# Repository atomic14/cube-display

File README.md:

# Cube Display

This is a work in progress project.

I'm currently testing the first set of PCBs. There will be updates as I find issues!

You can see some of the testing so far on my YouTube channel: [atomic14](https://www.youtube.com/@atomic14).

The demo above is using the code from [here](https://github.com/atomic14/ESP32-LSM6DS3-Demo).

# Files

- display-board: 14 segment display board
- main-board: main board for the display-board
- main-board-tft: WIP - not complete.

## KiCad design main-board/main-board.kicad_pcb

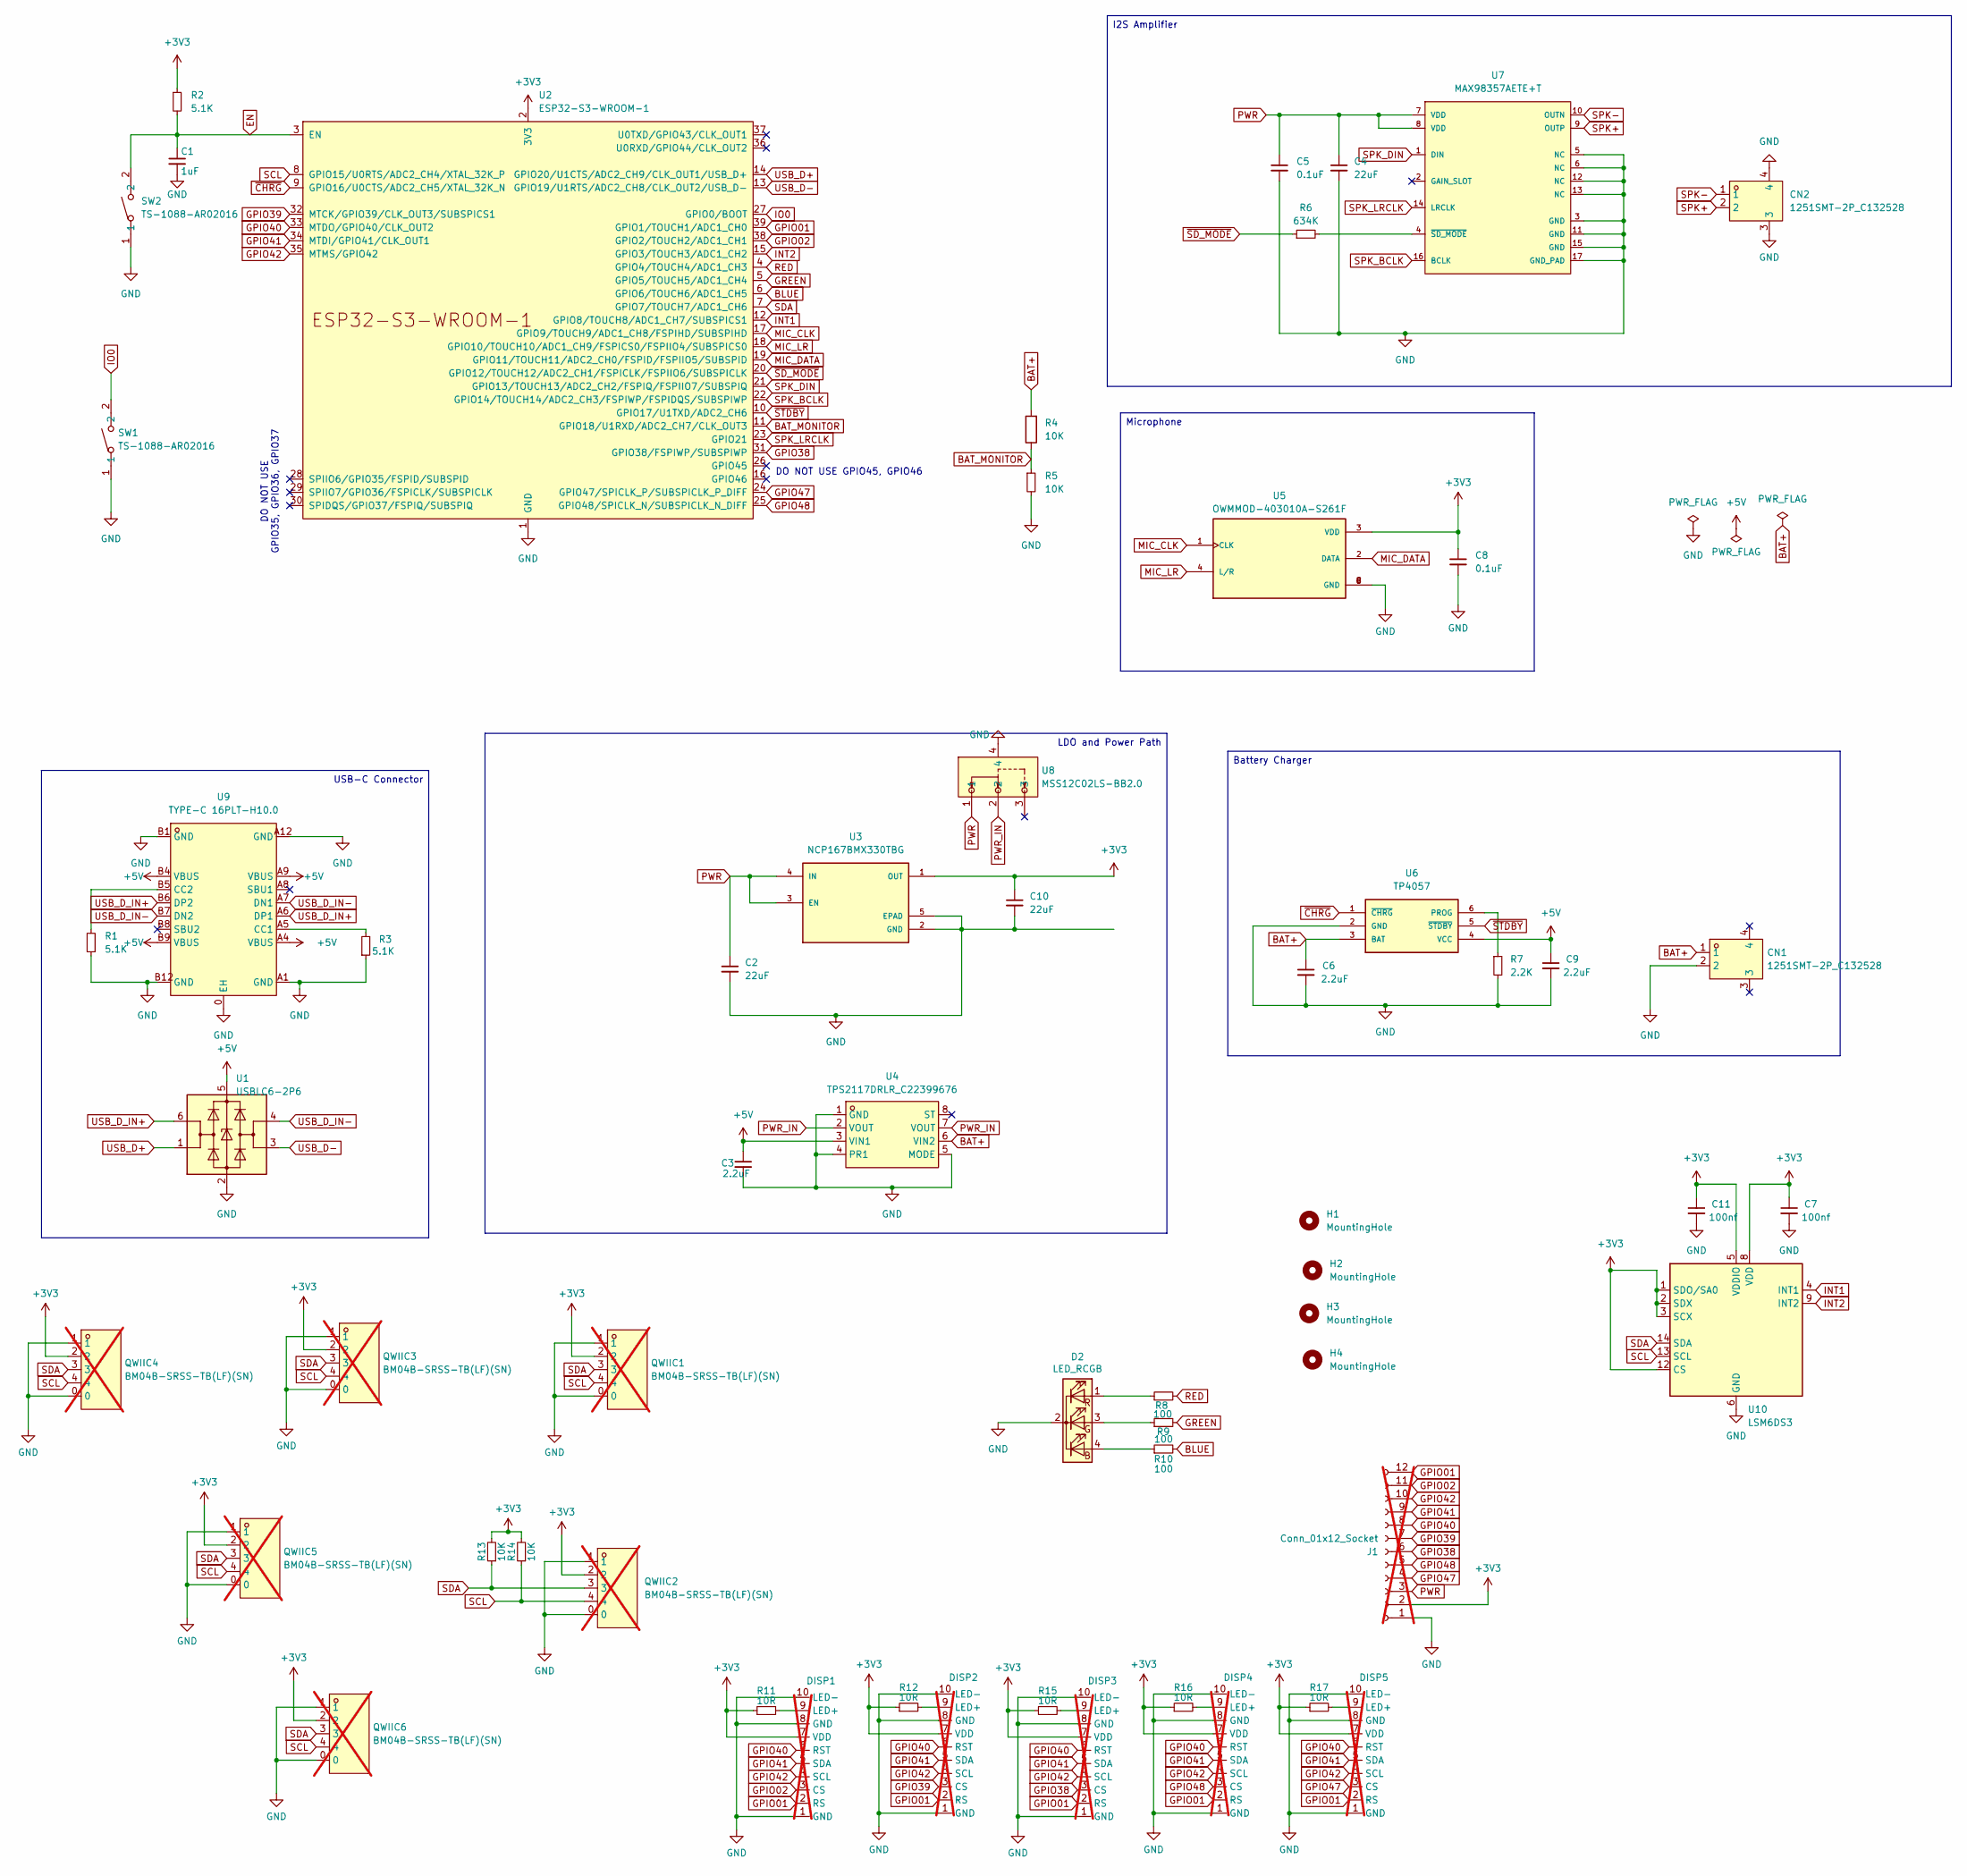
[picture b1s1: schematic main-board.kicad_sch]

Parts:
C1: 1uF; C_0402_1005Metric
C2, C4, C10: 22uF; C_0402_1005Metric
C3: 2.2uF; C_0402_1005Metric; Mfg Part # test
C5, C8: 0.1uF; C_0402_1005Metric
C6, C9: 2.2uF; C_0402_1005Metric
C7, C11: 100nf; C_0402_1005Metric
CN1, CN2: 1251SMT-2P_C132528; CONN-SMD_1251SMT-2P; LCSC Part C132528
D2: LED_RCGB; KAA-3528RGBS-11
DISP1, DISP2, DISP3, DISP4, DISP5: FPC_10_0.5; not fitted
H1, H2, H3, H4: MountingHole; MountingHole_2.2mm_M2
J1: Conn_01x12_Socket; PinSocket_1x12_P2.54mm_Vertical; not fitted
QWIIC1, QWIIC2, QWIIC3, QWIIC4, QWIIC5, QWIIC6: BM04B-SRSS-TB(LF)(SN); CONN-SMD_BM04B-SRSS-TB; LCSC Part C160390; not fitted
R1, R2, R3: 5.1K; R_0402_1005Metric
R4, R5, R13, R14: 10K; R_0402_1005Metric
R6: 634K; R_0402_1005Metric
R7: 2.2K; R_0402_1005Metric
R8, R9, R10: 100; R_0402_1005Metric
R11, R12, R15, R16, R17: 10R; R_0402_1005Metric
SW1, SW2: TS-1088-AR02016; SW-SMD_L3.9-W3.0-P4.45; LCSC Part C720477
U1: USBLC6-2P6; SOT-666
U2: ESP32-S3-WROOM-1
U3: NCP167BMX330TBG; VREG_NCP167BMX330TBG; PARTREV 5
U4: TPS2117DRLR_C22399676; SOT-583-8; LCSC Part C22399676
U5: OWMMOD-403010A-S261F; MIC_OWMMOD-403010A-S261F; PARTREV 00; DigiKey_Part_Number 3949-OWMMOD-403010A-S261F-ND
U6: TP4057; SOT-23-6
U7: MAX98357AETE+T; Maxim_Electronics-21-0896-0-0-0; mouser part number 700-MAX98357AETE+T; digikey description Amplifier IC 2-Channel (Stereo) Class D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
U8: MSS12C02LS-BB2.0; SW-SMD_MSS12C02LS-HB2.0-1; LCSC Part C3008585
U9: TYPE-C 16PLT-H10.0; TYPE-C-SMD_USB4120-03-C; LCSC Part C3151749
U10: LSM6DS3; LGA-14_3x2.5mm_P0.5mm_LayoutBorder3x4y

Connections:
+3V3: C7.1, C8.1, C10.1, C11.1, DISP1.7 (VDD), DISP2.7 (VDD), DISP3.7 (VDD), DISP4.7 (VDD), DISP5.7 (VDD), J1.2, QWIIC1.2, QWIIC2.2, QWIIC3.2, QWIIC4.2, QWIIC5.2, QWIIC6.2, R2.1, R11.1, R12.1, R13.2, R14.2, R15.1, R16.1, R17.1, U2.2 (3V3), U3.1 (OUT), U5.3 (VDD), U10.1 (SDO/SA0), U10.2 (SDX), U10.3 (SCX), U10.5 (VDDIO), U10.8 (VDD), U10.12 (CS)
+5V: C3.1, C9.1, U1.5 (VBUS), U4.3 (VIN1), U6.4 (VCC), U9.A4 (VBUS), U9.A9 (VBUS), U9.B4 (VBUS), U9.B9 (VBUS)
BAT+: C6.1, CN1.1, R4.2, U4.6 (VIN2), U6.3 (BAT)
BAT_MONITOR: R4.1, R5.1, U2.11 (GPIO18/U1RXD/ADC2_CH7/CLK_OUT3)
BLUE: R10.2, U2.6 (GPIO6/TOUCH6/ADC1_CH5)
EN: C1.1, R2.2, SW2.2, U2.3 (EN)
GND: C1.2, C2.2, C3.2, C4.2, C5.2, C6.2, C7.2, C8.2, C9.2, C10.2, C11.2, CN1.2, CN2.3, CN2.4, D2.2 (K), DISP1.1 (GND), DISP1.8 (GND), DISP1.10 (LED-), DISP2.1 (GND), DISP2.8 (GND), DISP2.10 (LED-), DISP3.1 (GND), DISP3.8 (GND), DISP3.10 (LED-), DISP4.1 (GND), DISP4.8 (GND), DISP4.10 (LED-), DISP5.1 (GND), DISP5.8 (GND), DISP5.10 (LED-), J1.1, QWIIC1.0, QWIIC1.1, QWIIC2.0, QWIIC2.1, QWIIC3.0, QWIIC3.1, QWIIC4.0, QWIIC4.1, QWIIC5.0, QWIIC5.1, QWIIC6.0, QWIIC6.1, R1.1, R3.1, R5.2, R7.2, SW1.1, SW2.1, U1.2 (GND), U2.1 (GND), U2.40 (GND), U2.41 (GND), U3.2 (GND), U3.5 (EPAD), U4.1 (GND), U4.4 (PR1), U4.5 (MODE), U5.5 (GND), U5.6 (GND), U5.7 (GND), U5.8 (GND), U6.2 (GND), U7.3 (GND), U7.5 (NC), U7.6 (NC), U7.11 (GND), U7.12 (NC), U7.13 (NC), U7.15 (GND), U7.17 (GND_PAD), U8.4, U9.0 (EH), U9.A1 (GND), U9.A12 (GND), U9.B1 (GND), U9.B12 (GND), U10.6 (GND), U10.7 (GND)
GPIO01: DISP1.2 (RS), DISP2.2 (RS), DISP3.2 (RS), DISP4.2 (RS), DISP5.2 (RS), J1.12, U2.39 (GPIO1/TOUCH1/ADC1_CH0)
GPIO02: DISP1.3 (CS), J1.11, U2.38 (GPIO2/TOUCH2/ADC1_CH1)
GPIO38: DISP3.3 (CS), J1.6, U2.31 (GPIO38/FSPIWP/SUBSPIWP)
GPIO39: DISP2.3 (CS), J1.7, U2.32 (MTCK/GPIO39/CLK_OUT3/SUBSPICS1)
GPIO40: DISP1.6 (RST), DISP2.6 (RST), DISP3.6 (RST), DISP4.6 (RST), DISP5.6 (RST), J1.8, U2.33 (MTDO/GPIO40/CLK_OUT2)
GPIO41: DISP1.5 (SDA), DISP2.5 (SDA), DISP3.5 (SDA), DISP4.5 (SDA), DISP5.5 (SDA), J1.9, U2.34 (MTDI/GPIO41/CLK_OUT1)
GPIO42: DISP1.4 (SCL), DISP2.4 (SCL), DISP3.4 (SCL), DISP4.4 (SCL), DISP5.4 (SCL), J1.10, U2.35 (MTMS/GPIO42)
GPIO47: DISP5.3 (CS), J1.4, U2.24 (GPIO47/SPICLK_P/SUBSPICLK_P_DIFF)
GPIO48: DISP4.3 (CS), J1.5, U2.25 (GPIO48/SPICLK_N/SUBSPICLK_N_DIFF)
GREEN: R9.2, U2.5 (GPIO5/TOUCH5/ADC1_CH4)
INT1: U2.12 (GPIO8/TOUCH8/ADC1_CH7/SUBSPICS1), U10.4 (INT1)
INT2: U2.15 (GPIO3/TOUCH3/ADC1_CH2), U10.9 (INT2)
IO0: SW1.2, U2.27 (GPIO0/BOOT)
MIC_CLK: U2.17 (GPIO9/TOUCH9/ADC1_CH8/FSPIHD/SUBSPIHD), U5.1 (CLK)
MIC_DATA: U2.19 (GPIO11/TOUCH11/ADC2_CH0/FSPID/FSPIIO5/S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), U5.2 (DATA)
MIC_LR: U2.18 (GPIO10/TOUCH10/ADC1_CH9/FSPICS0/FSPIIO4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), U5.4 (L/R)
unnamed: D2.4 (BA), R10.1
unnamed: D2.3 (GA), R9.1
unnamed: D2.1 (RA), R8.1
unnamed: DISP1.9 (LED+), R11.2
unnamed: DISP2.9 (LED+), R12.2
unnamed: DISP3.9 (LED+), R15.2
unnamed: DISP4.9 (LED+), R16.2
unnamed: DISP5.9 (LED+), R17.2
unnamed: R7.1, U6.6 (PROG)
unnamed: R6.2, U7.4 (~SD_MODE)
unnamed: R3.2, U9.A5 (CC1)
unnamed: R1.2, U9.B5 (CC2)
PWR: C2.1, C4.1, C5.1, J1.3, U3.3 (EN), U3.4 (IN), U7.7 (VDD), U7.8 (VDD), U8.1
PWR_IN: U4.2 (VOUT), U4.7 (VOUT), U8.2
RED: R8.2, U2.4 (GPIO4/TOUCH4/ADC1_CH3)
SCL: QWIIC1.4, QWIIC2.4, QWIIC3.4, QWIIC4.4, QWIIC5.4, QWIIC6.4, R14.1, U2.8 (GPIO15/U0RTS/ADC2_CH4/XTAL_32K_P), U10.13 (SCL)
SDA: QWIIC1.3, QWIIC2.3, QWIIC3.3, QWIIC4.3, QWIIC5.3, QWIIC6.3, R13.1, U2.7 (GPIO7/TOUCH7/ADC1_CH6), U10.14 (SDA)
SPK+: CN2.2, U7.9 (OUTP)
SPK-: CN2.1, U7.10 (OUTN)
SPK_BCLK: U2.22 (GPIO14/TOUCH14/ADC2_CH3/FSPIWP/FSPIDQS/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), U7.16 (BCLK)
SPK_DIN: U2.21 (GPIO13/TOUCH13/ADC2_CH2/FSPIQ/FSPIIO7/S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), U7.1 (DIN)
SPK_LRCLK: U2.23 (GPIO21), U7.14 (LRCLK)
USB_D+: U1.1 (I/O1), U2.14 (GPIO20/U1CTS/ADC2_CH9/CLK_OUT1/USB_D+)
USB_D-: U1.3 (I/O2), U2.13 (GPIO19/U1RTS/ADC2_CH8/CLK_OUT2/USB_D-)
USB_D_IN+: U1.6 (I/O1), U9.A6 (DP1), U9.B6 (DP2)
USB_D_IN-: U1.4 (I/O2), U9.A7 (DN1), U9.B7 (DN2)
~CHRG: U2.9 (GPIO16/U0CTS/ADC2_CH5/XTAL_32K_N), U6.1 (~CHRG)
~SD_MODE: R6.1, U2.20 (GPIO12/TOUCH12/ADC2_CH1/FSPICLK/FSPIIO6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)
~STDBY: U2.10 (GPIO17/U1TXD/ADC2_CH6), U6.5 (~STDBY)

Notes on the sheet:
DO NOT USE GPIO35, GPIO36, GPIO37
DO NOT USE GPIO45, GPIO46
Battery Charger
USB-C Connector
I2S Amplifier
Microphone
LDO and Power Path

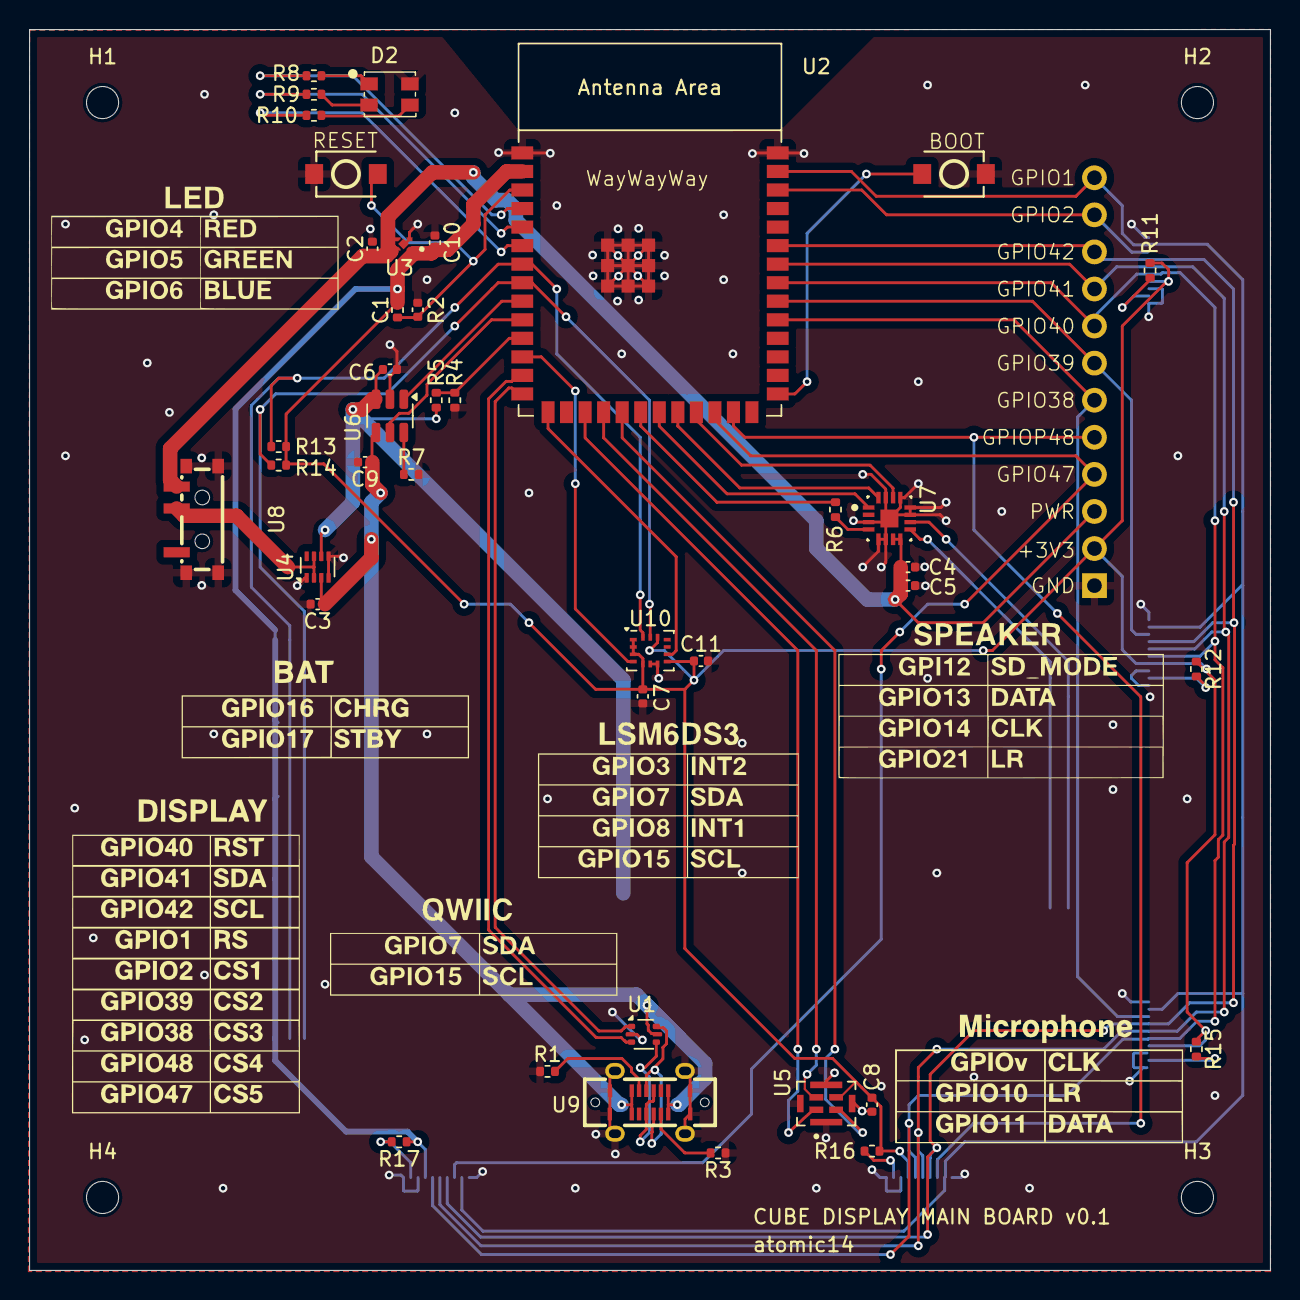
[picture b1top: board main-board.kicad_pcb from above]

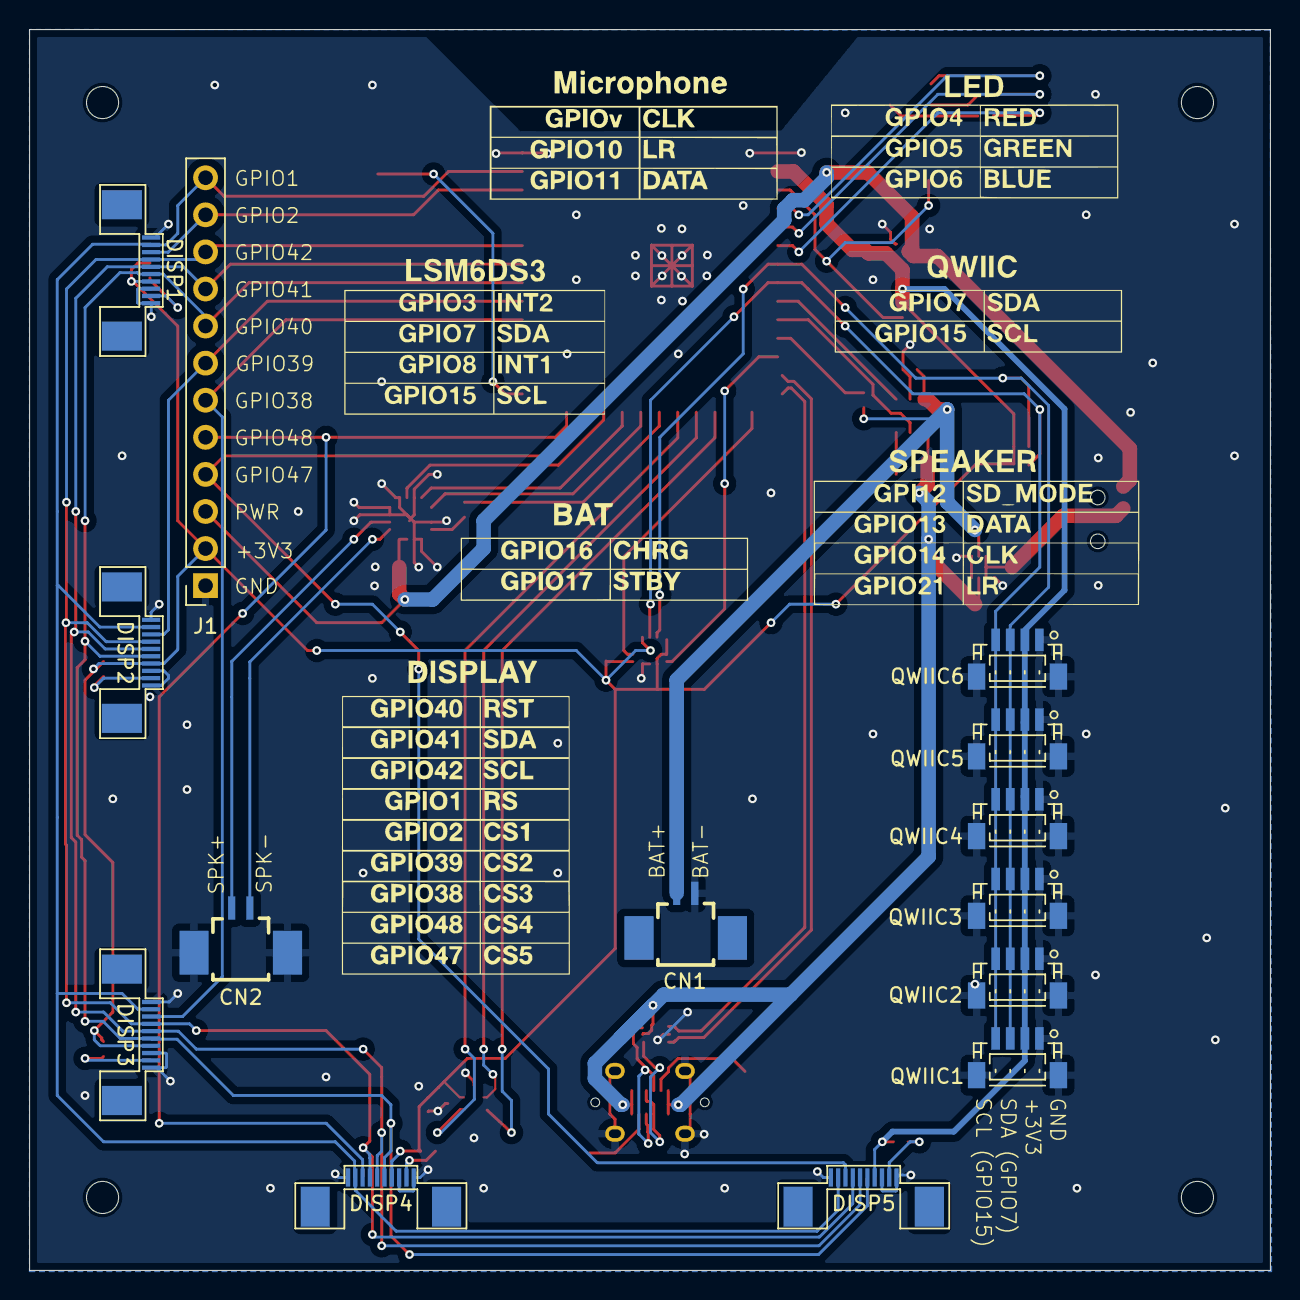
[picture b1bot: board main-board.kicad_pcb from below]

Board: 2 copper layers, 85.0 x 85.0 mm, 59 parts (14 on the bottom side), 52 nets.

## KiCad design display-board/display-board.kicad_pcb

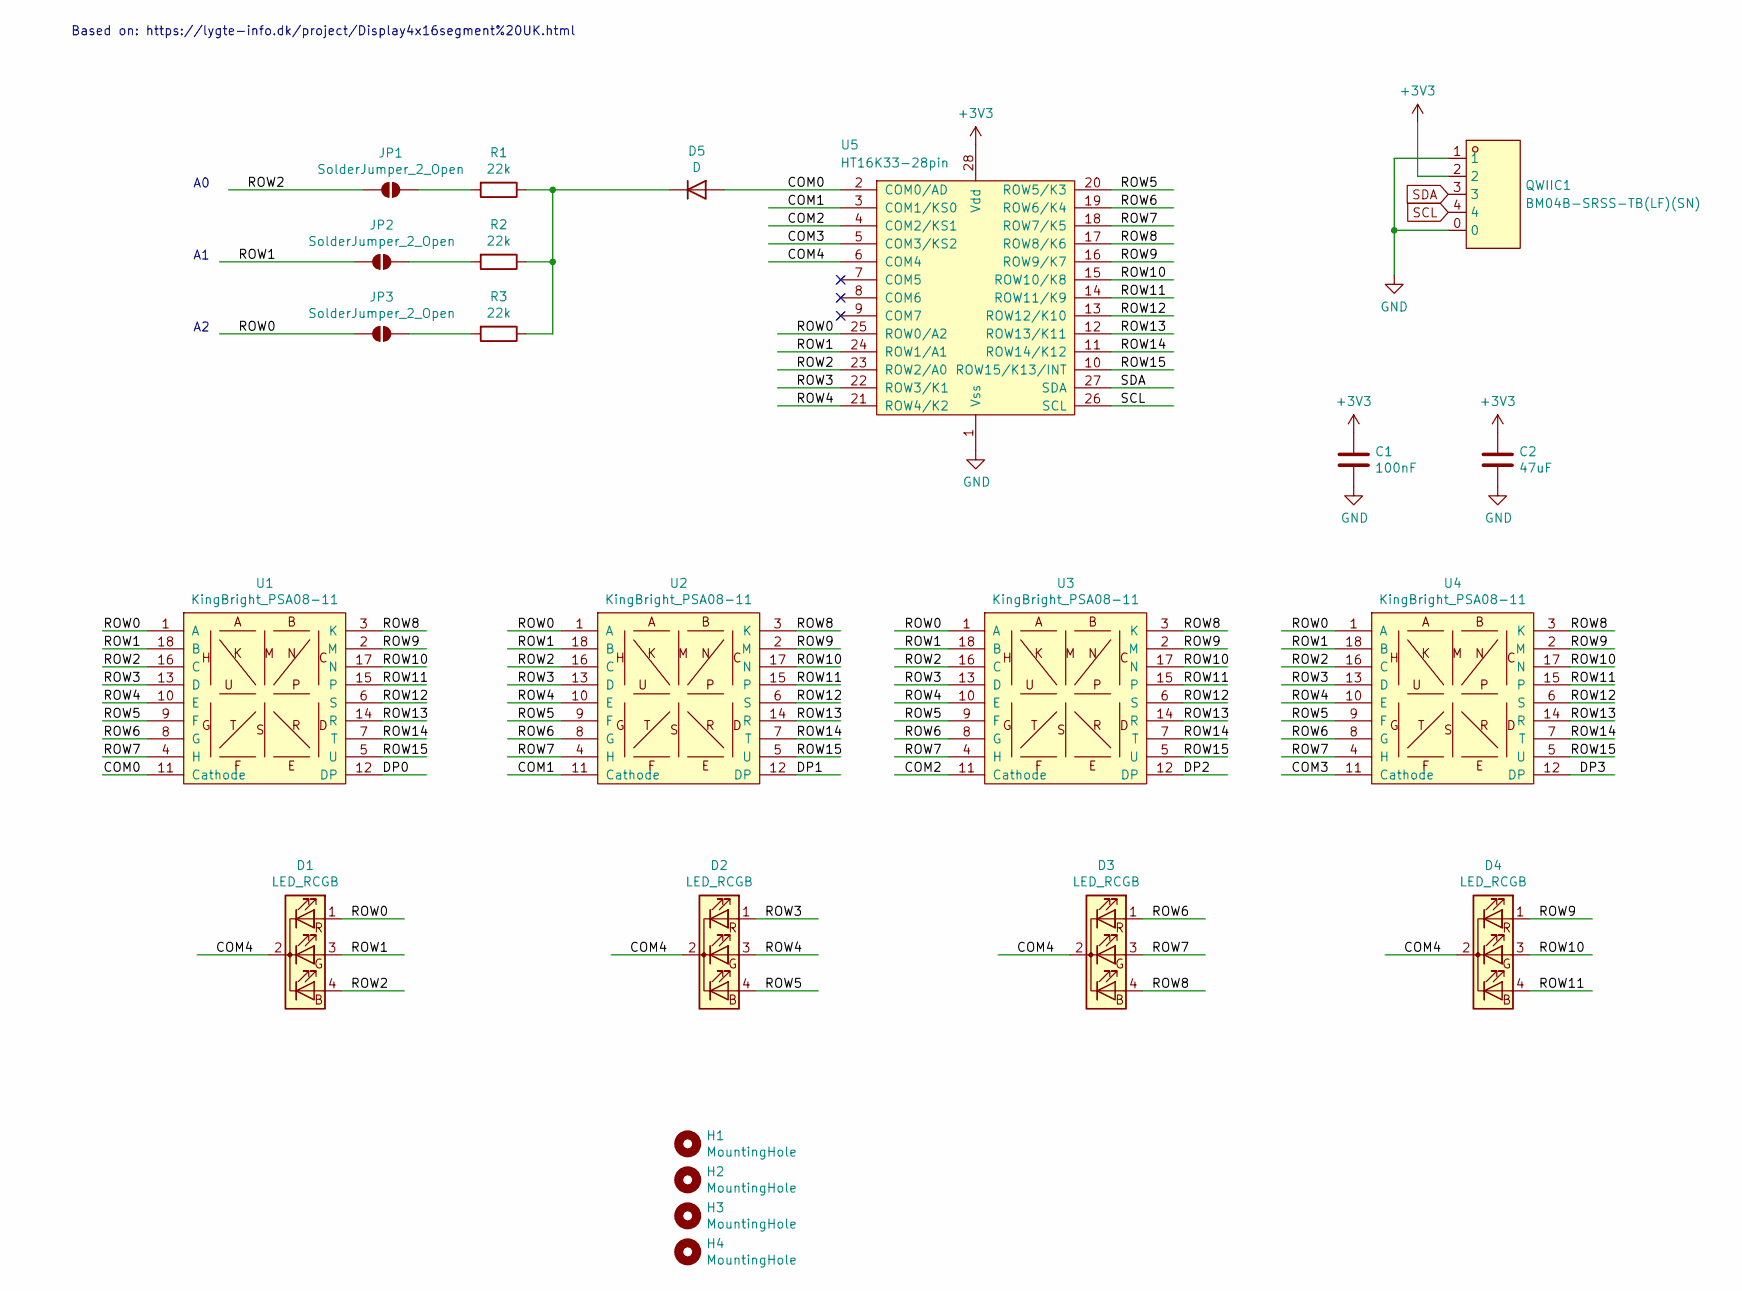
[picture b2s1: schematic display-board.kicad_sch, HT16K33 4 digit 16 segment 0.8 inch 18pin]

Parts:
C1: 100nF; C_0603_1608Metric
C2: 47uF; C_0603_1608Metric
D1, D2, D3, D4: LED_RCGB; KAA-3528RGBS-11
D5: D; D_SOD-323
H1, H2, H3, H4: MountingHole; MountingHole_2.2mm_M2
JP1, JP2, JP3: SolderJumper_2_Open; SolderJumper-2_P1.3mm_Open_RoundedPad1.0x1.5mm
QWIIC1: BM04B-SRSS-TB(LF)(SN); CONN-SMD_BM04B-SRSS-TB; LCSC Part C160390
R1, R2, R3: 22k; R_0603_1608Metric
U1, U2, U3, U4: KingBright_PSA08-11; DIP-18_600_ELL
U5: HT16K33-28pin; SOIC-28W_7.5x18.7mm_P1.27mm

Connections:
+3V3: C1.1, C2.1, QWIIC1.2, U5.28 (Vdd)
/COM0: D5.2 (A), U1.11 (Cathode), U5.2 (COM0/AD)
/COM1: U2.11 (Cathode), U5.3 (COM1/KS0)
/COM2: U3.11 (Cathode), U5.4 (COM2/KS1)
/COM3: U4.11 (Cathode), U5.5 (COM3/KS2)
/COM4: D1.2 (K), D2.2 (K), D3.2 (K), D4.2 (K), U5.6 (COM4)
/DP0: U1.12 (DP)
/DP1: U2.12 (DP)
/DP2: U3.12 (DP)
/DP3: U4.12 (DP)
/ROW0: D1.1 (RA), JP3.1 (A), U1.1 (A), U2.1 (A), U3.1 (A), U4.1 (A), U5.25 (ROW0/A2)
/ROW1: D1.3 (GA), JP2.1 (A), U1.18 (B), U2.18 (B), U3.18 (B), U4.18 (B), U5.24 (ROW1/A1)
/ROW2: D1.4 (BA), JP1.1 (A), U1.16 (C), U2.16 (C), U3.16 (C), U4.16 (C), U5.23 (ROW2/A0)
/ROW3: D2.1 (RA), U1.13 (D), U2.13 (D), U3.13 (D), U4.13 (D), U5.22 (ROW3/K1)
/ROW4: D2.3 (GA), U1.10 (E), U2.10 (E), U3.10 (E), U4.10 (E), U5.21 (ROW4/K2)
/ROW5: D2.4 (BA), U1.9 (F), U2.9 (F), U3.9 (F), U4.9 (F), U5.20 (ROW5/K3)
/ROW6: D3.1 (RA), U1.8 (G), U2.8 (G), U3.8 (G), U4.8 (G), U5.19 (ROW6/K4)
/ROW7: D3.3 (GA), U1.4 (H), U2.4 (H), U3.4 (H), U4.4 (H), U5.18 (ROW7/K5)
/ROW8: D3.4 (BA), U1.3 (K), U2.3 (K), U3.3 (K), U4.3 (K), U5.17 (ROW8/K6)
/ROW9: D4.1 (RA), U1.2 (M), U2.2 (M), U3.2 (M), U4.2 (M), U5.16 (ROW9/K7)
/ROW10: D4.3 (GA), U1.17 (N), U2.17 (N), U3.17 (N), U4.17 (N), U5.15 (ROW10/K8)
/ROW11: D4.4 (BA), U1.15, U2.15, U3.15, U4.15, U5.14 (ROW11/K9)
/ROW12: U1.6 (S), U2.6 (S), U3.6 (S), U4.6 (S), U5.13 (ROW12/K10)
/ROW13: U1.14 (R), U2.14 (R), U3.14 (R), U4.14 (R), U5.12 (ROW13/K11)
/ROW14: U1.7 (T), U2.7 (T), U3.7 (T), U4.7 (T), U5.11 (ROW14/K12)
/ROW15: U1.5 (U), U2.5 (U), U3.5 (U), U4.5 (U), U5.10 (ROW15/K13/INT)
GND: C1.2, C2.2, QWIIC1.0, QWIIC1.1, U5.1 (Vss)
unnamed: D5.1 (K), R1.1, R2.1, R3.1
unnamed: JP1.2 (B), R1.2
unnamed: JP2.2 (B), R2.2
unnamed: JP3.2 (B), R3.2
SCL: QWIIC1.4, U5.26 (SCL)
SDA: QWIIC1.3, U5.27 (SDA)

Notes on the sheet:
Based on: https://lygte-info.dk/project/Display4x16segment%20UK.html

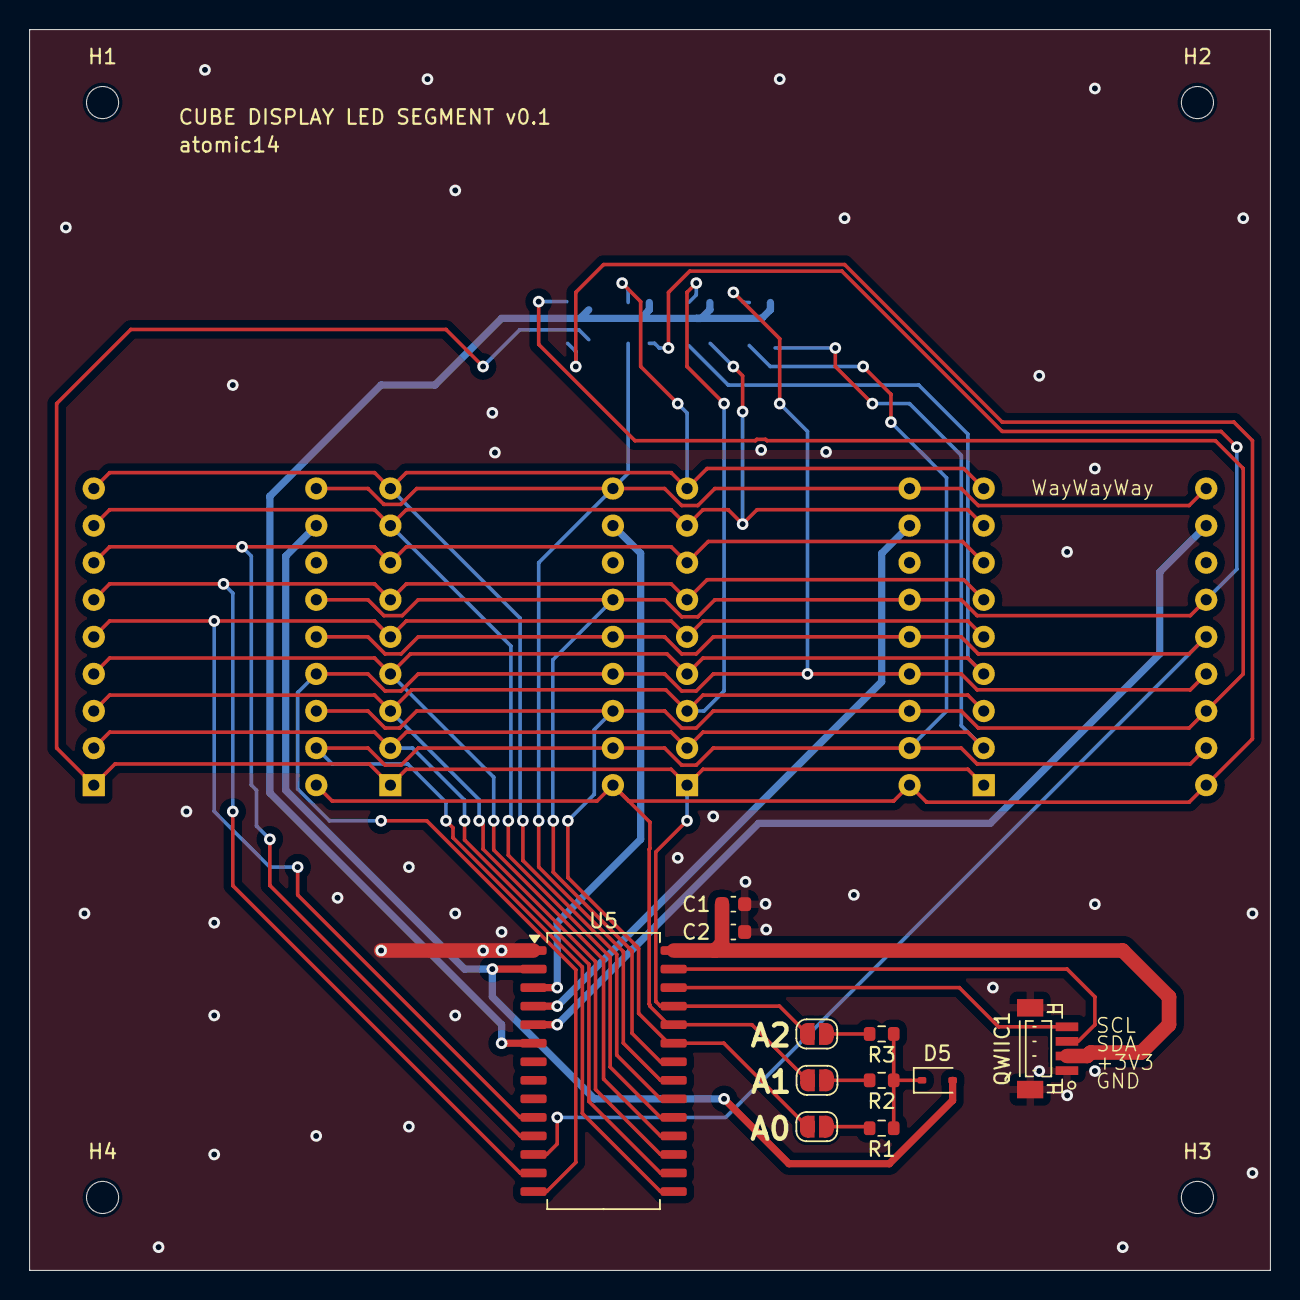
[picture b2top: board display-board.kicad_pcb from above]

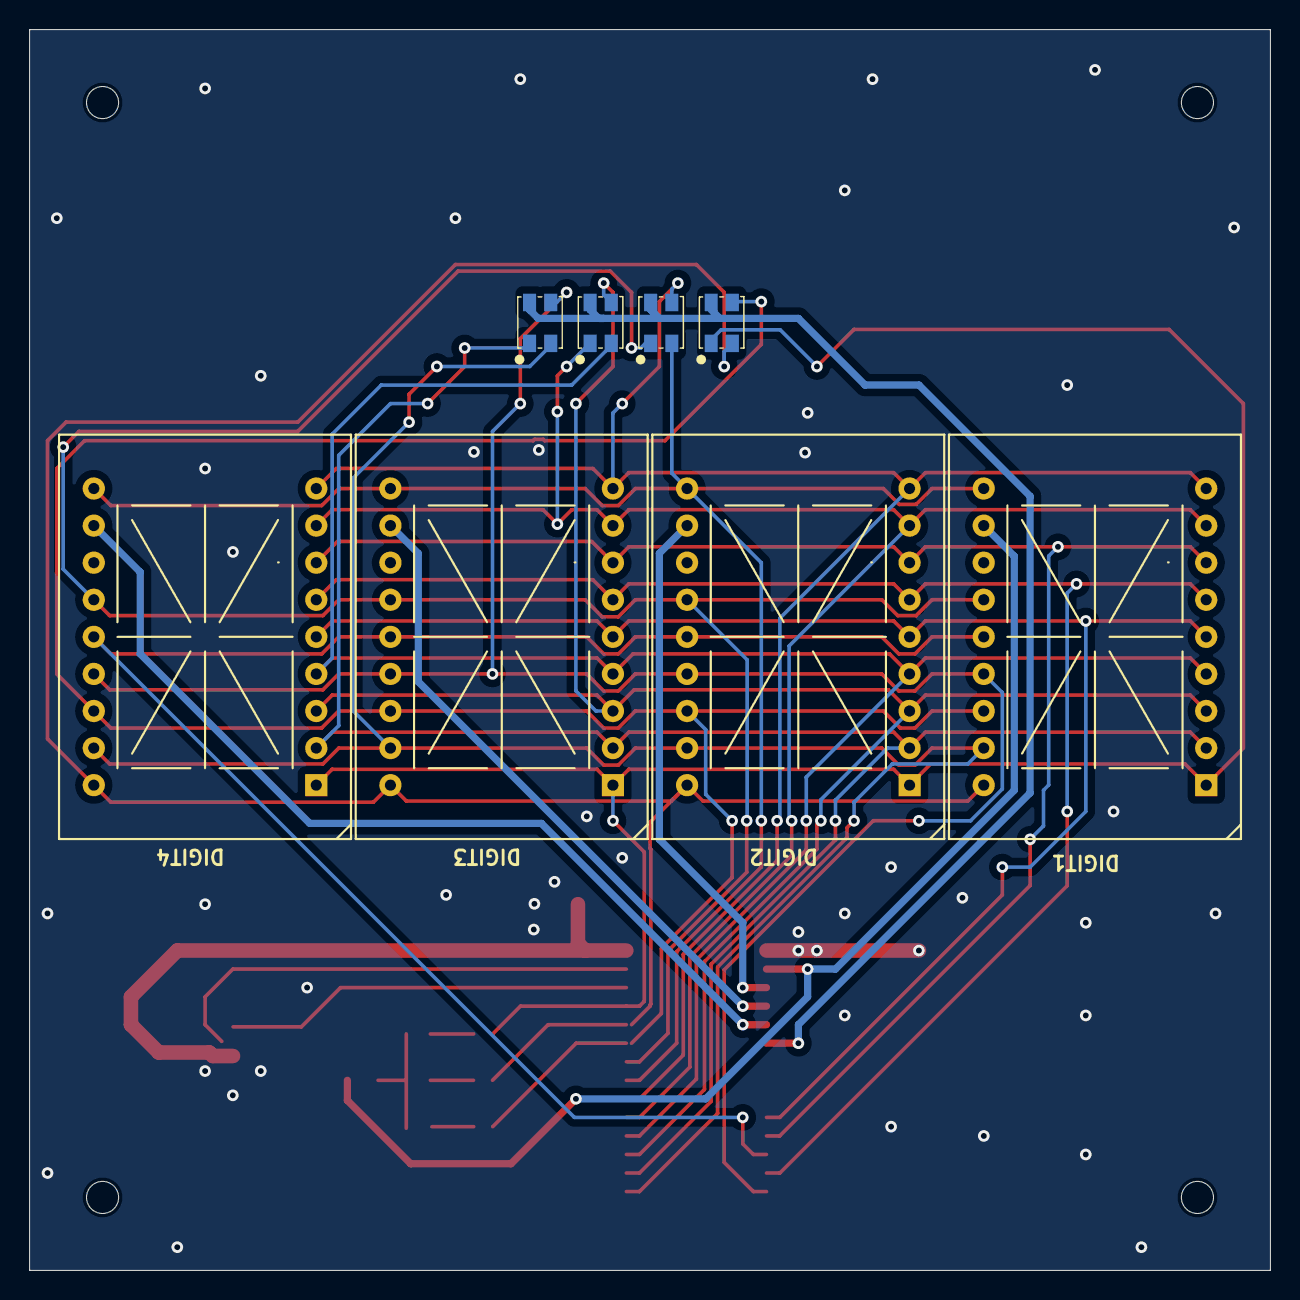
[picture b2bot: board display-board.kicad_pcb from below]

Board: 2 copper layers, 85.0 x 85.0 mm, 23 parts (8 on the bottom side), 29 nets.
